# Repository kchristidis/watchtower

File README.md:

# Watchtower

NC State ECE Senior Design Project, Fall 2015

## Description

Monitor the state of a building (temperature, luminosity, number of people) with easy-to-deploy Pi-based sensor boxes and an intuitive Web interface.

Allow others to access a sensor box you own using the dashboard.

Use the REST API to programmatically export sensor data, and build applications on top of **Watchtower**.

[Video presentation](https://www.youtube.com/watch?v=rJIvThQTJWE) of the project on Design Day: 24m01s to 25m02s

## Contents

  - Source code for the Web interface
  - Schematics for the Pi PCB
  - Scripts for the Pi
  - Screenshots
  - Documentation

## Credits

Coded by:
  - Andrew Kofink <ajkofink@ncsu.edu>
  - Spencer Hitchins <jshitchi@ncsu.edu>
  - Scott Whalen <swwhalen@ncsu.edu>

Mentored by:
  - Kostas Christidis <kchrist@ncsu.edu>
  - Michael Devetsikiotis <mdevets@ncsu.edu>

Sponsored by: 
  - IBM

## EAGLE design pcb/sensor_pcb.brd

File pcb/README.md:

- `sensor_pcb.brd` is the board file for EagleCAD for the PCB in our project that connects to the Raspberry Pi
  - `sensor_pcb.sch` is the schematic file for EagleCAD for the PCB in our project that connects to the Raspberry Pi
  - `gerber-files` contains all the files needed when sending the PCB to a manufacturer

When soldering the sensors on there is a label next to each set of wholes on the top side saying which sensor goes where, and on the under side shows a `V` for where the positive voltage pin should go. For a more simple explanation of how to orient the sensors, when looking at the side with the name labels and with the double row of pin wholes on the top you want each sensor to be mostly to the right of the pin wholes that go with that sensor.

Scott Whalen
swwhalen@ncsu.edu

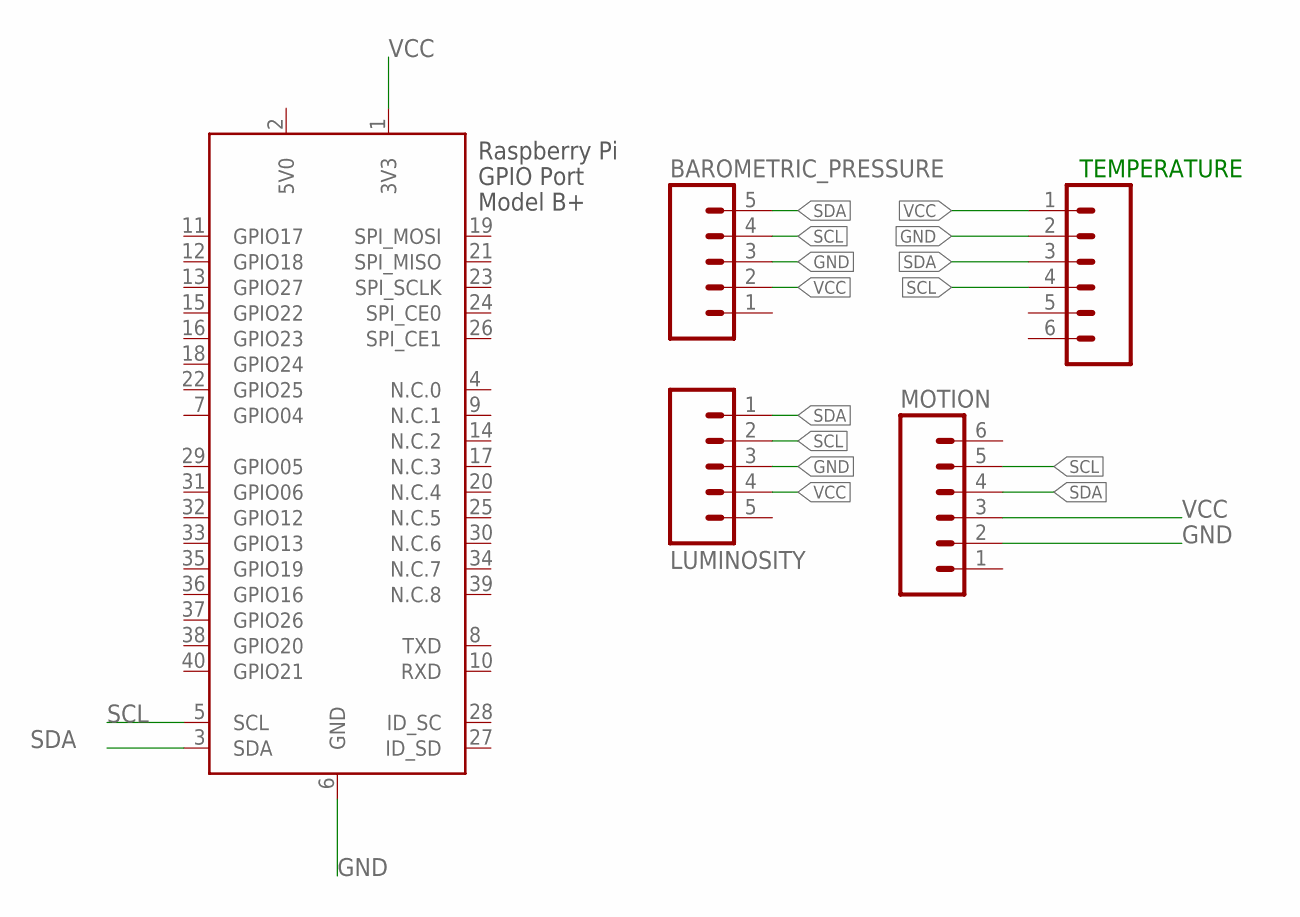
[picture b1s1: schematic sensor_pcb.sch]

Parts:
BAROMETRIC_PRESSURE: M05_ROUNDONLY_NOSILK; 1X05_ROUNDONLY_NOSILK
LUMINOSITY: M05_ROUNDONLY_NOSILK; 1X05_ROUNDONLY_NOSILK
MOTION: M06SIP; 1X06
TEMPERATURE: M06SIP; 1X06
X1: RASPI_BOARD_B+_E0; RASPI_BOARD_B+_EDGES_0DRILL

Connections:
5V0: X1.2 (5V0)
GND: BAROMETRIC_PRESSURE.3, LUMINOSITY.3, MOTION.2, TEMPERATURE.2, X1.6 (GND)
SCL: BAROMETRIC_PRESSURE.4, LUMINOSITY.2, MOTION.5, TEMPERATURE.4, X1.5 (SCL)
SDA: BAROMETRIC_PRESSURE.5, LUMINOSITY.1, MOTION.4, TEMPERATURE.3, X1.3 (SDA)
VCC: BAROMETRIC_PRESSURE.2, LUMINOSITY.4, MOTION.3, TEMPERATURE.1, X1.1 (3V3)

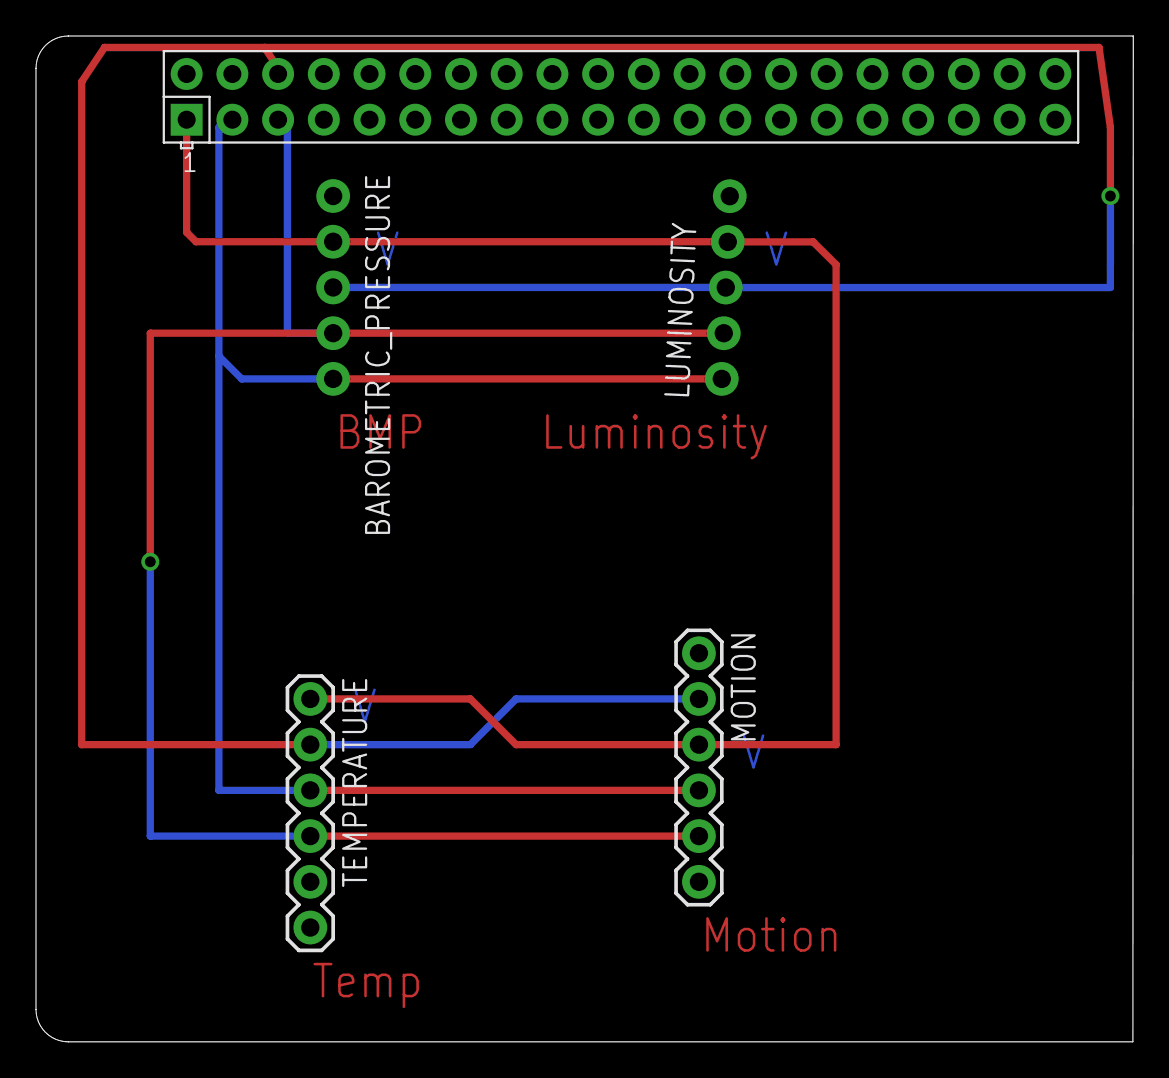
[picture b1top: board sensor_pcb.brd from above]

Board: 2 copper layers, 61.0 x 55.9 mm, 5 parts (0 on the bottom side), 4 nets.

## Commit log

2015-12-30 Add project deliverables
2015-12-30 Add license
2016-01-04 Link to Design Day video
2016-01-23 Fix line breaks in license file

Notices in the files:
parts and their libraries:
SparkFun-Connectors: Licensing: CC v3.0 Share-Alike You are welcome to use this library for commercial purposes.
